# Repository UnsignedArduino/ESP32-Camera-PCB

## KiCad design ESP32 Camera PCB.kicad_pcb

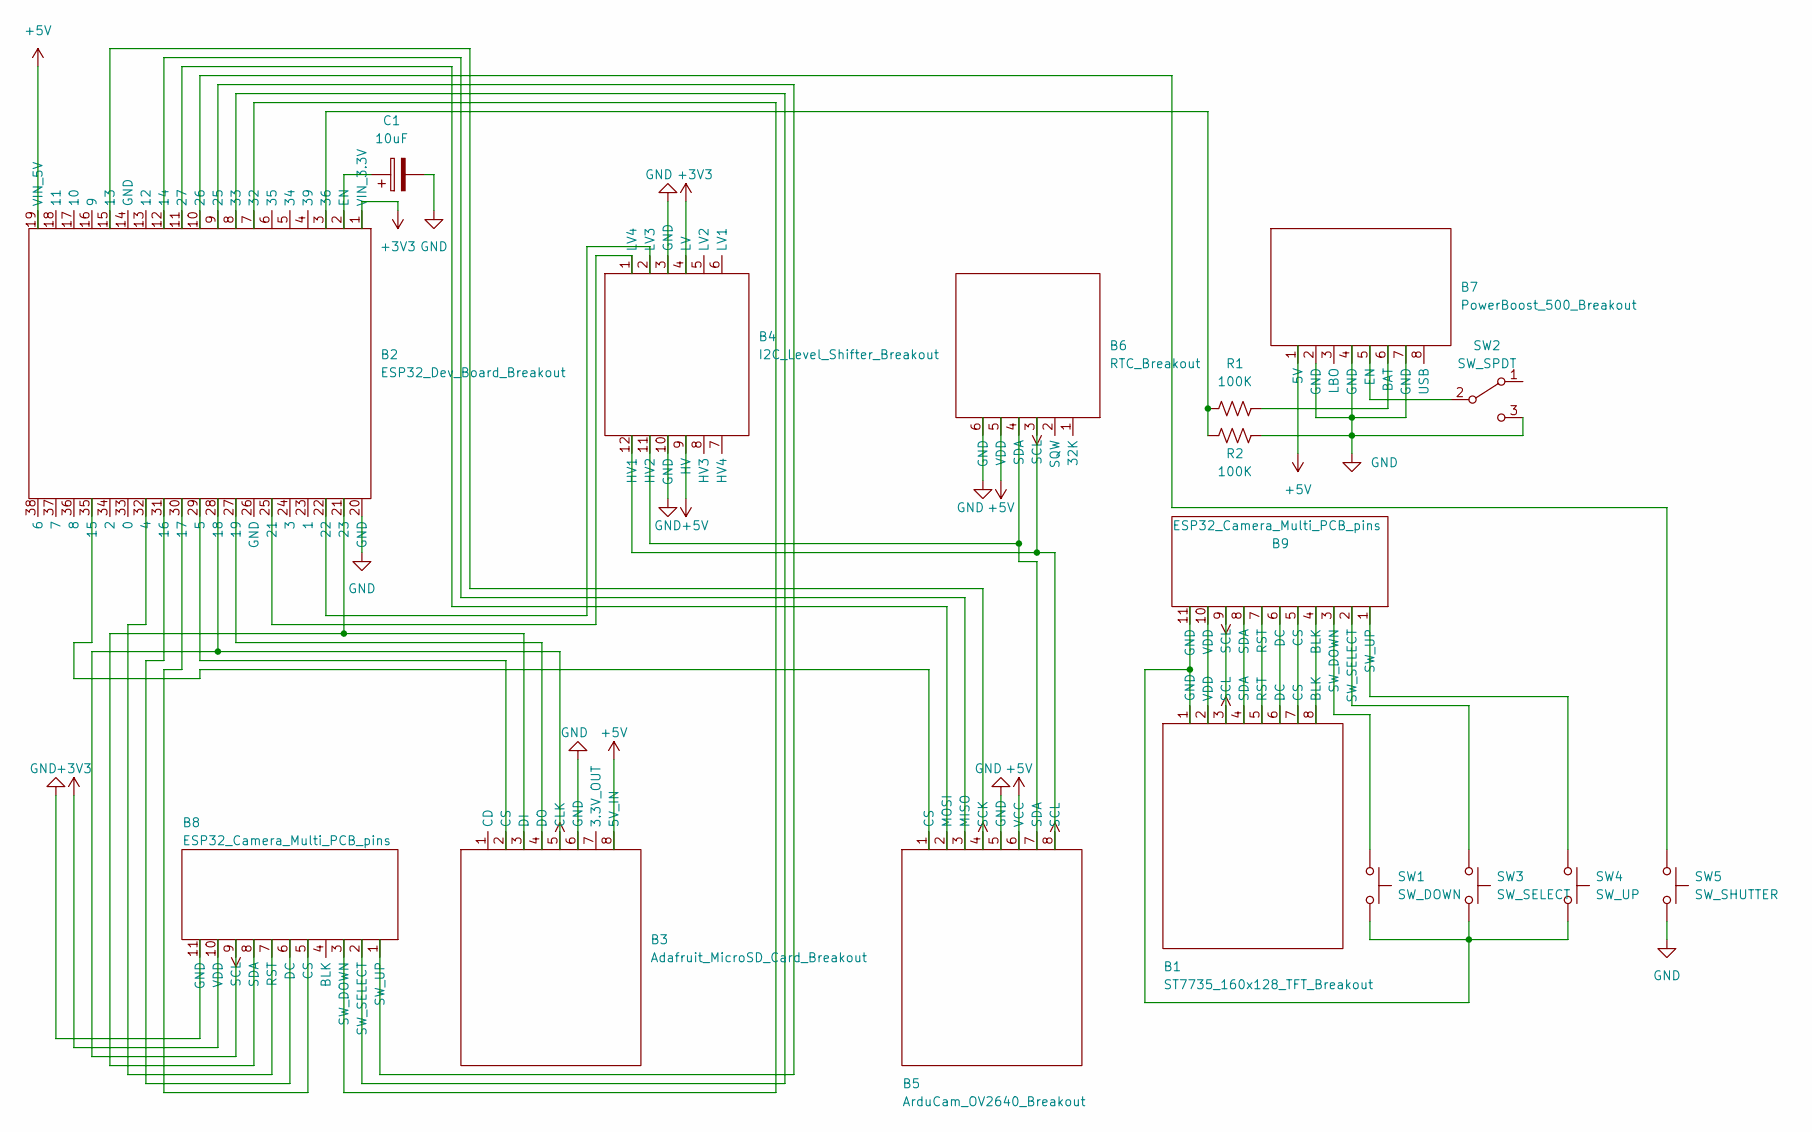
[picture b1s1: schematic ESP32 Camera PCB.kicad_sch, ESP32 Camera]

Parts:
B1: ST7735_160x128_TFT_Breakout
B2: ESP32_Dev_Board_Breakout
B3: Adafruit_MicroSD_Card_Breakout
B4: I2C_Level_Shifter_Breakout
B5: ArduCam_OV2640_Breakout
B6: RTC_Breakout
B7: PowerBoost_500_Breakout; Adafruit_PowerBoost_500_Breakout
B8, B9: ESP32_Camera_Multi_PCB_pins
C1: 10uF; CP_Radial_D5.0mm_P2.50mm
R1, R2: 100K; R_Axial_DIN0207_L6.3mm_D2.5mm_P10.16mm_Horizontal
SW1: SW_DOWN; SW_PUSH-12mm
SW2: SW_SPDT; SW_Slide_1P2T_CK_OS102011MS2Q
SW3: SW_SELECT; SW_PUSH-12mm
SW4: SW_UP; SW_PUSH-12mm
SW5: SW_SHUTTER; SW_PUSH-12mm

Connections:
+3V3: B2.1 (VIN_3.3V), B4.4 (LV), B8.10 (VDD)
+5V: B2.19 (VIN_5V), B3.8 (5V_IN), B4.9 (HV), B5.6 (VCC), B6.5 (VDD), B7.1 (5V)
GND: B3.6 (GND), B4.3 (GND), B4.10 (GND), B5.5 (GND), B6.6 (GND), B7.4 (GND), B7.7 (GND), B8.11 (GND), C1.2, R2.1, SW2.3 (C), SW5.2
unnamed: B1.1 (GND), B9.11 (GND), SW1.2, SW3.2, SW4.2
unnamed: B1.2 (VDD), B9.10 (VDD)
unnamed: B1.3 (SCL), B9.9 (SCL)
unnamed: B1.4 (SDA), B9.8 (SDA)
unnamed: B1.5 (RST), B9.7 (RST)
unnamed: B1.6 (DC), B9.6 (DC)
unnamed: B1.7 (CS), B9.5 (CS)
unnamed: B1.8 (BLK), B9.4 (BLK)
unnamed: B2.2 (EN), C1.1
unnamed: B2.3 (36), R1.1, R2.2
unnamed: B2.7 (32), B8.3 (SW_DOWN)
unnamed: B2.8 (33), B8.2 (SW_SELECT)
unnamed: B2.9 (25), B8.1 (SW_UP)
unnamed: B2.10 (26), SW5.1
unnamed: B2.11 (27), B5.2 (MOSI)
unnamed: B2.12 (14), B5.3 (MISO)
unnamed: B2.15 (13), B5.4 (SCK)
unnamed: B2.21 (23), B3.3 (DI), B8.8 (SDA)
unnamed: B2.22, B4.2 (LV3)
unnamed: B2.25 (21), B4.1 (LV4)
unnamed: B2.27 (19), B3.4 (DO)
unnamed: B2.28 (18), B3.5 (CLK), B8.9 (SCL)
unnamed: B2.29 (5), B3.2 (CS)
unnamed: B2.30 (17), B8.5 (CS)
unnamed: B2.31 (16), B8.6 (DC)
unnamed: B2.32 (4), B8.7 (RST)
unnamed: B2.35 (15), B5.1 (CS)
unnamed: B4.11 (HV2), B5.7 (SDA), B6.4 (SDA)
unnamed: B4.12 (HV1), B5.8 (SCL), B6.3 (SCL)
unnamed: B7.5 (EN), SW2.2 (B)
unnamed: B7.6 (BAT), R1.2
unnamed: B9.1 (SW_UP), SW4.1
unnamed: B9.2 (SW_SELECT), SW3.1
unnamed: B9.3 (SW_DOWN), SW1.1

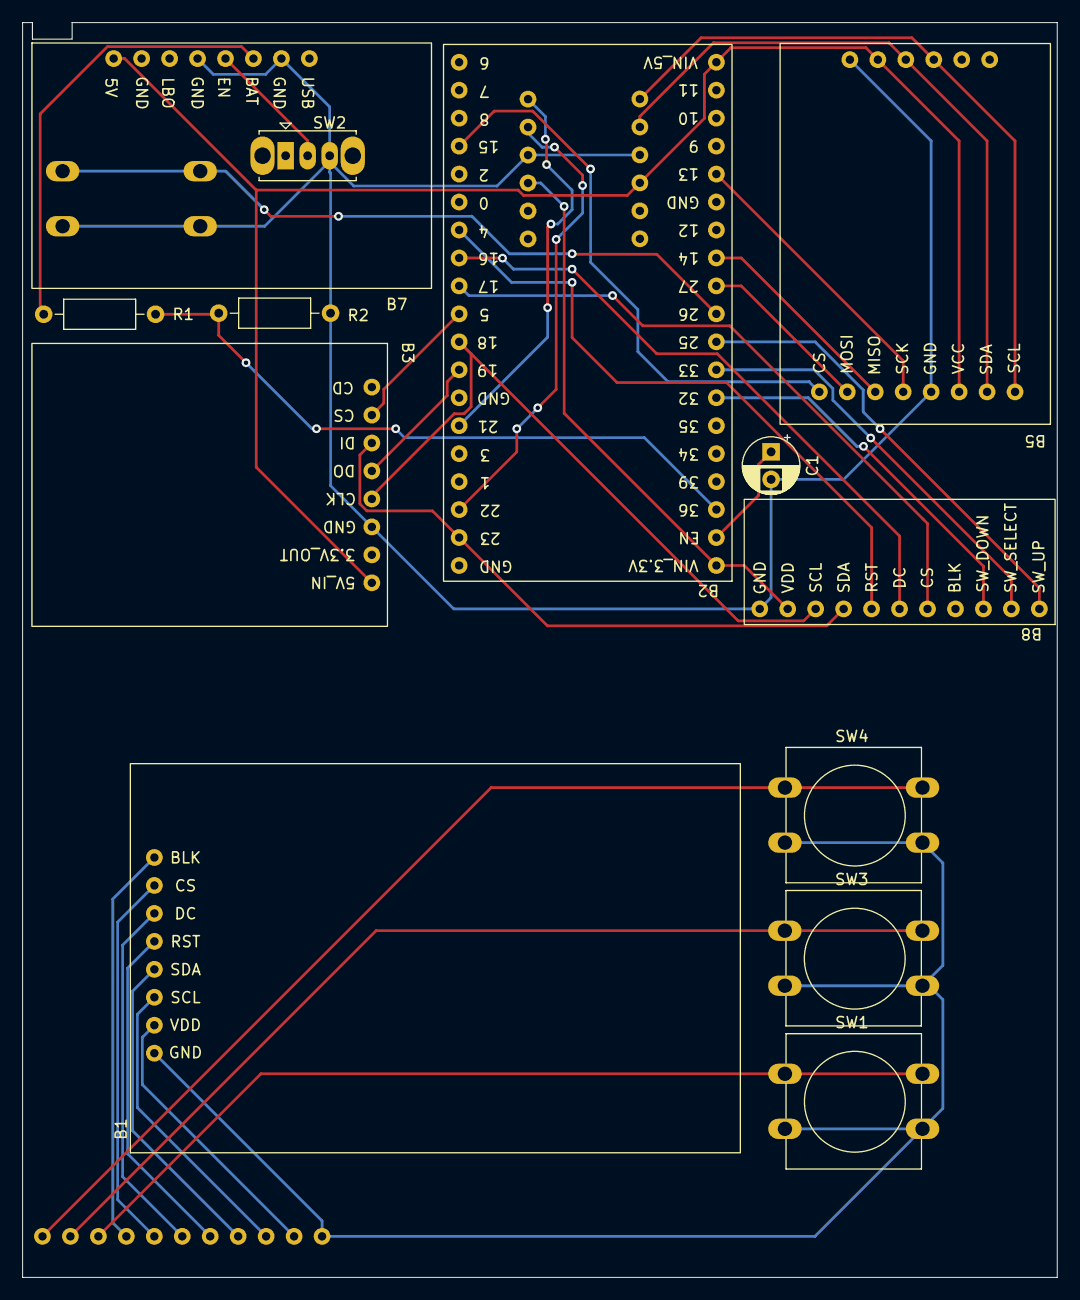
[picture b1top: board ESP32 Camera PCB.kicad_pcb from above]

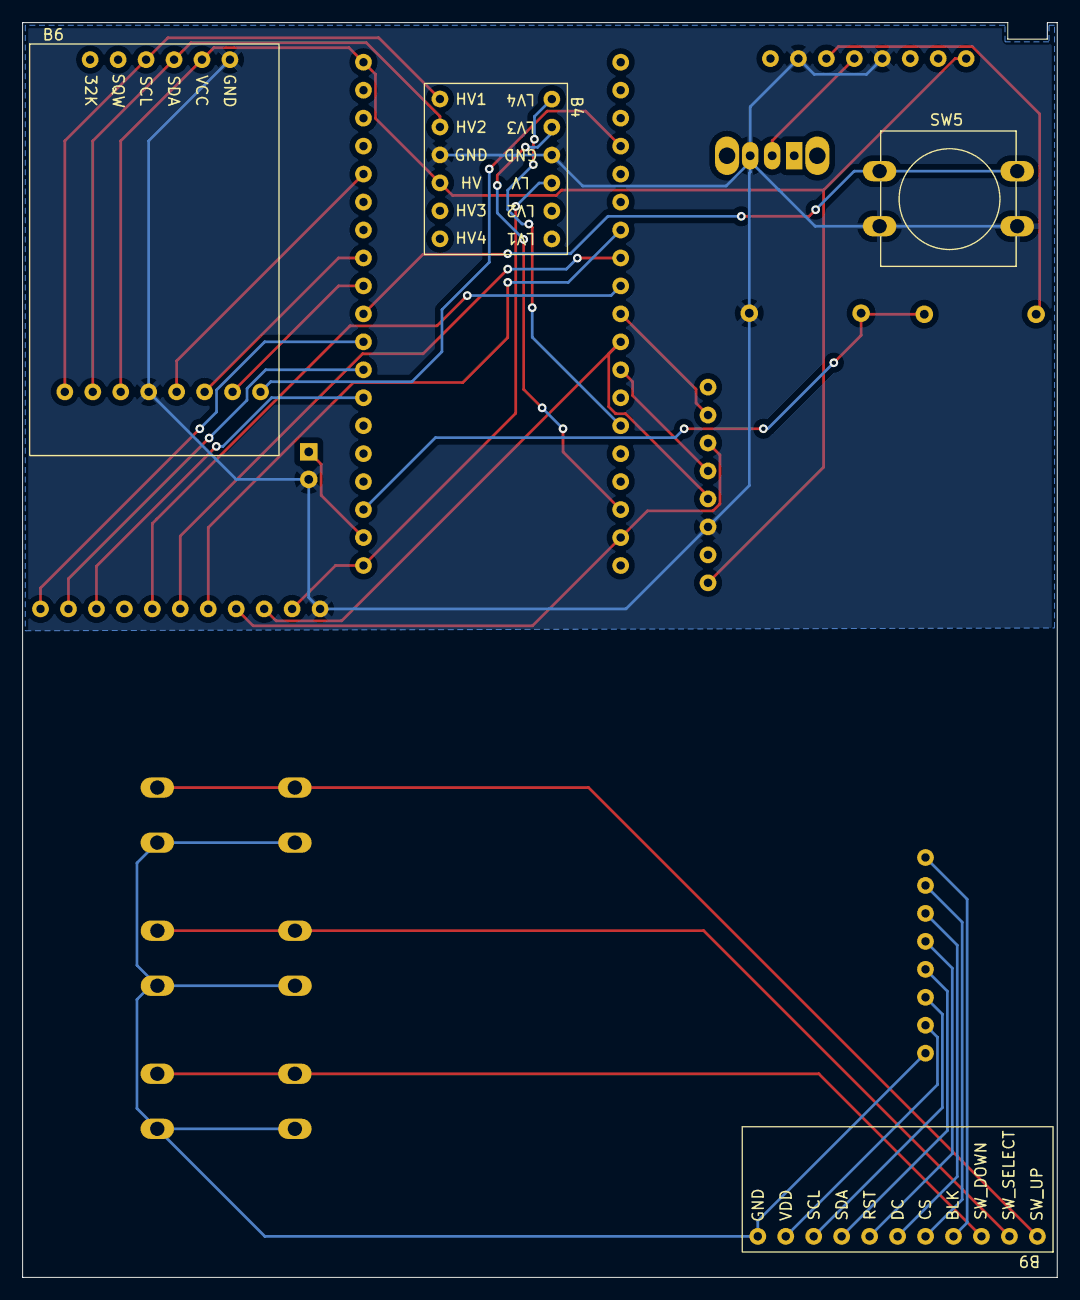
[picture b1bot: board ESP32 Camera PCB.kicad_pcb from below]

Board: 2 copper layers, 94.0 x 114.0 mm, 17 parts (4 on the bottom side), 37 nets.

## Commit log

2023-02-03 Initial design
